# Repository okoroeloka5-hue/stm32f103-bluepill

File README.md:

# Basic STM32 Bluepill Based Board

KiCAD PCB Design based on the STM32 Bluepill. Done with guidance from Phil's Lab STM32 PCB Design Tutorial from [Youtube](https://www.youtube.com/watch?v=aVUqaB0IMh4).

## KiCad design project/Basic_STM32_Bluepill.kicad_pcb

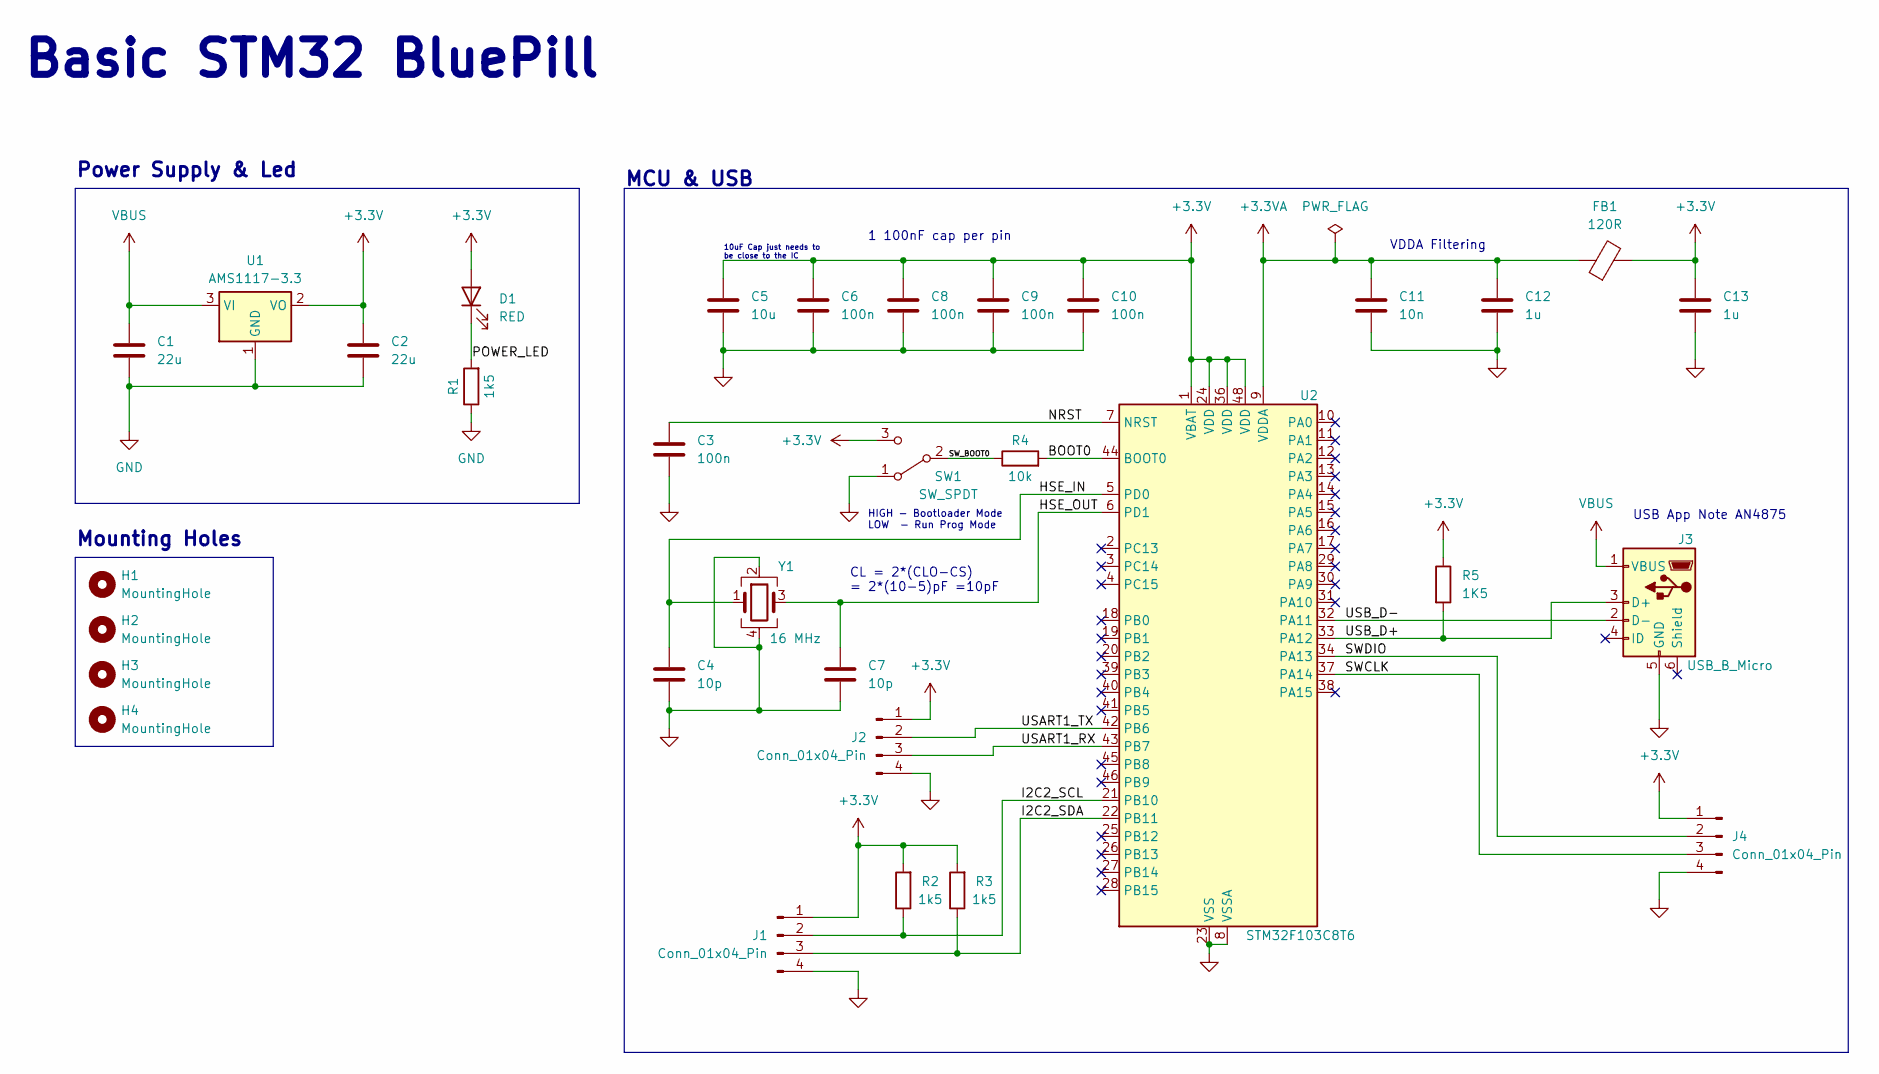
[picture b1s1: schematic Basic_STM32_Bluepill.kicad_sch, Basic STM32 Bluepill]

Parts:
C1, C2: 22u; C_0805_2012Metric
C3, C6, C8, C9, C10: 100n; C_0402_1005Metric
C4, C7: 10p; C_0402_1005Metric
C5: 10u; C_0603_1608Metric
C11: 10n; C_0402_1005Metric
C12, C13: 1u; C_0402_1005Metric
D1: RED; LED_0603_1608Metric
FB1: 120R; L_0603_1608Metric
H1, H2, H3, H4: MountingHole; MountingHole_2.2mm_M2
J1, J2, J4: Conn_01x04_Pin; PinHeader_1x04_P2.54mm_Vertical
J3: USB_B_Micro; USB_Micro-B_Wuerth_629105150521
R1, R2, R3: 1k5; R_0402_1005Metric
R4: 10k; R_0402_1005Metric
R5: 1K5; R_0402_1005Metric
SW1: SW_SPDT; SW_SPDT_PCM12
U1: AMS1117-3.3; SOT-223-3_TabPin2
U2: STM32F103C8T6; LQFP-48_7x7mm_P0.5mm
Y1: 16 MHz; Crystal_SMD_3225-4Pin_3.2x2.5mm

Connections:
+3.3V: C2.1, C5.1, C6.1, C8.1, C9.1, C10.1, C13.1, D1.2 (A), FB1.2, J1.1, J2.1, J4.1, R2.2, R3.2, R5.1, SW1.3 (C), U1.2 (VO), U2.1 (VBAT), U2.24 (VDD), U2.36 (VDD), U2.48 (VDD)
+3.3VA: C11.1, C12.1, FB1.1, U2.9 (VDDA)
/BOOT0: R4.2, U2.44 (BOOT0)
/HSE_IN: C4.1, U2.5 (PD0), Y1.1
/HSE_OUT: C7.1, U2.6 (PD1), Y1.3
/I2C2_SCL: J1.2, R2.1, U2.21 (PB10)
/I2C2_SDA: J1.3, R3.1, U2.22 (PB11)
/NRST: C3.1, U2.7 (NRST)
/POWER_LED: D1.1 (K), R1.2
/SWCLK: J4.3, U2.37 (PA14)
/SWDIO: J4.2, U2.34 (PA13)
/SW_BOOT0: R4.1, SW1.2 (B)
/USART1_RX: J2.3, U2.43 (PB7)
/USART1_TX: J2.2, U2.42 (PB6)
/USB_D+: J3.3 (D+), R5.2, U2.33 (PA12)
/USB_D-: J3.2 (D-), U2.32 (PA11)
GND: C1.2, C2.2, C3.2, C4.2, C5.2, C6.2, C7.2, C8.2, C9.2, C10.2, C11.2, C12.2, C13.2, J1.4, J2.4, J3.5 (GND), J4.4, R1.1, SW1.1 (A), U1.1 (GND), U2.8 (VSSA), U2.23 (VSS), U2.35 (VSS), U2.47 (VSS), Y1.2, Y1.4
VBUS: C1.1, J3.1 (VBUS), U1.3 (VI)

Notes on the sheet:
Power Supply & Led
Mounting Holes
USB App Note AN4875
10uF Cap just needs to be close to the IC
HIGH - Bootloader Mode LOW - Run Prog Mode
VDDA Filtering
CL = 2*(CLO-CS) = 2*(10-5)pF =10pF
Basic STM32 BluePill
MCU & USB
1 100nF cap per pin

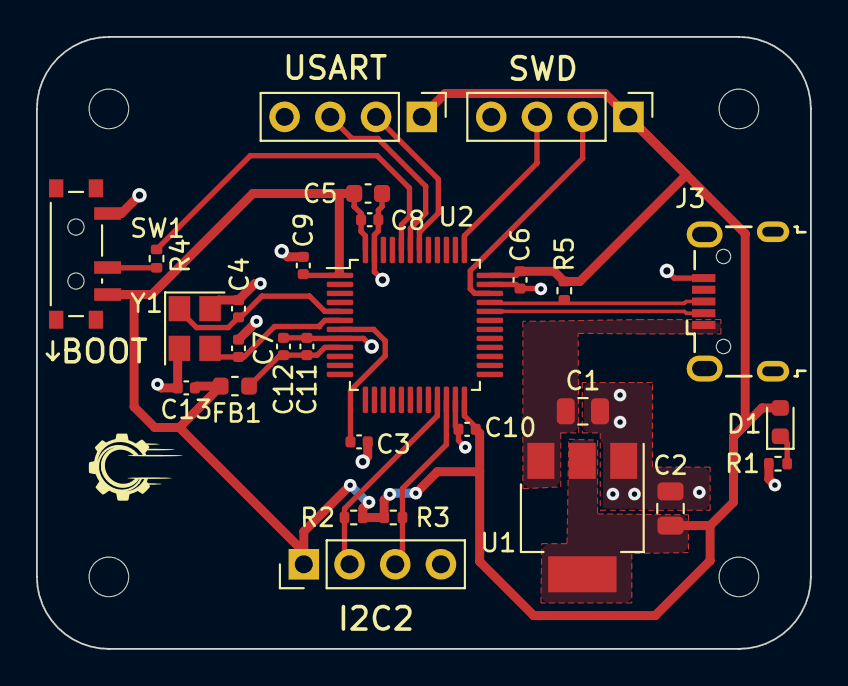
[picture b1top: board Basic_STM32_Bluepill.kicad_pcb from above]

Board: 2 copper layers, 43.0 x 34.0 mm, 32 parts (0 on the bottom side), 18 nets.
